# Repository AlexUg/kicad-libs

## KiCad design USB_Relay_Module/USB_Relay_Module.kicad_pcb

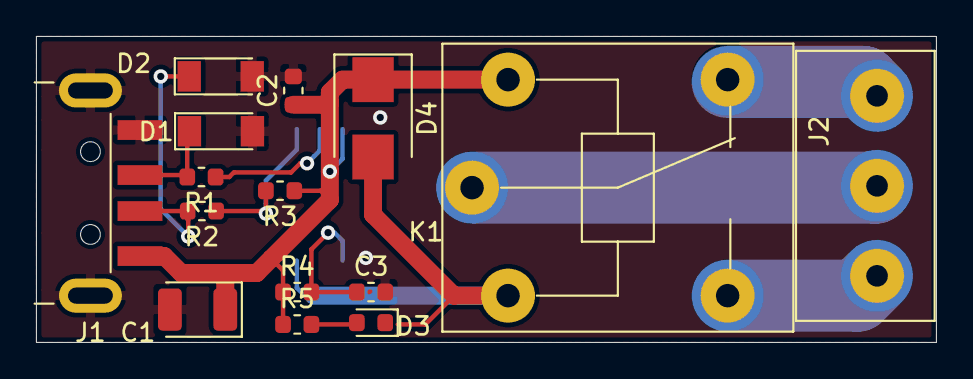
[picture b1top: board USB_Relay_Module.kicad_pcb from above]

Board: 2 copper layers, 50.0 x 17.0 mm, 16 parts (1 on the bottom side), 12 nets.

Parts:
C1: 47uF; CP_EIA-3528-12_Kemet-T
C2, C3: 100n; C_0603_1608Metric
D1, D2: 3.6V; D_MiniMELF
D3: LED; LED_0603_1608Metric
D4: D; D_SMB
J1: USB_A; USB_A_CNCTech_1001-011-01101_Horizontal
J2: OUT; KF301_5.0_3
K1: HLS8
R1, R2: 82; R_0603_1608Metric
R3, R5: 880; R_0603_1608Metric
R4: 10k; R_0603_1608Metric
U1: ATtiny45-20SU; SOIJ-8_5.3x5.3mm_P1.27mm

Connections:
02: J2.2, K1.5
03: J2.1, K1.3
+5V: C1.1, C2.1, D4.1, J1.1, K1.1, R3.1, R4.1, R5.1, U1.8
D+: R1.1, U1.7
D-: R2.1, R3.2, U1.6
GND: C1.2, C2.2, C3.2, D1.2, D2.2, J1.4, J1.5, U1.4
unnamed: D1.1, J1.3, R1.2
unnamed: D2.1, J1.2, R2.2
unnamed: D3.2, R5.2
O1: J2.3, K1.2
Rel: D3.1, D4.2, K1.4, U1.3
Reset: C3.1, R4.2, U1.1

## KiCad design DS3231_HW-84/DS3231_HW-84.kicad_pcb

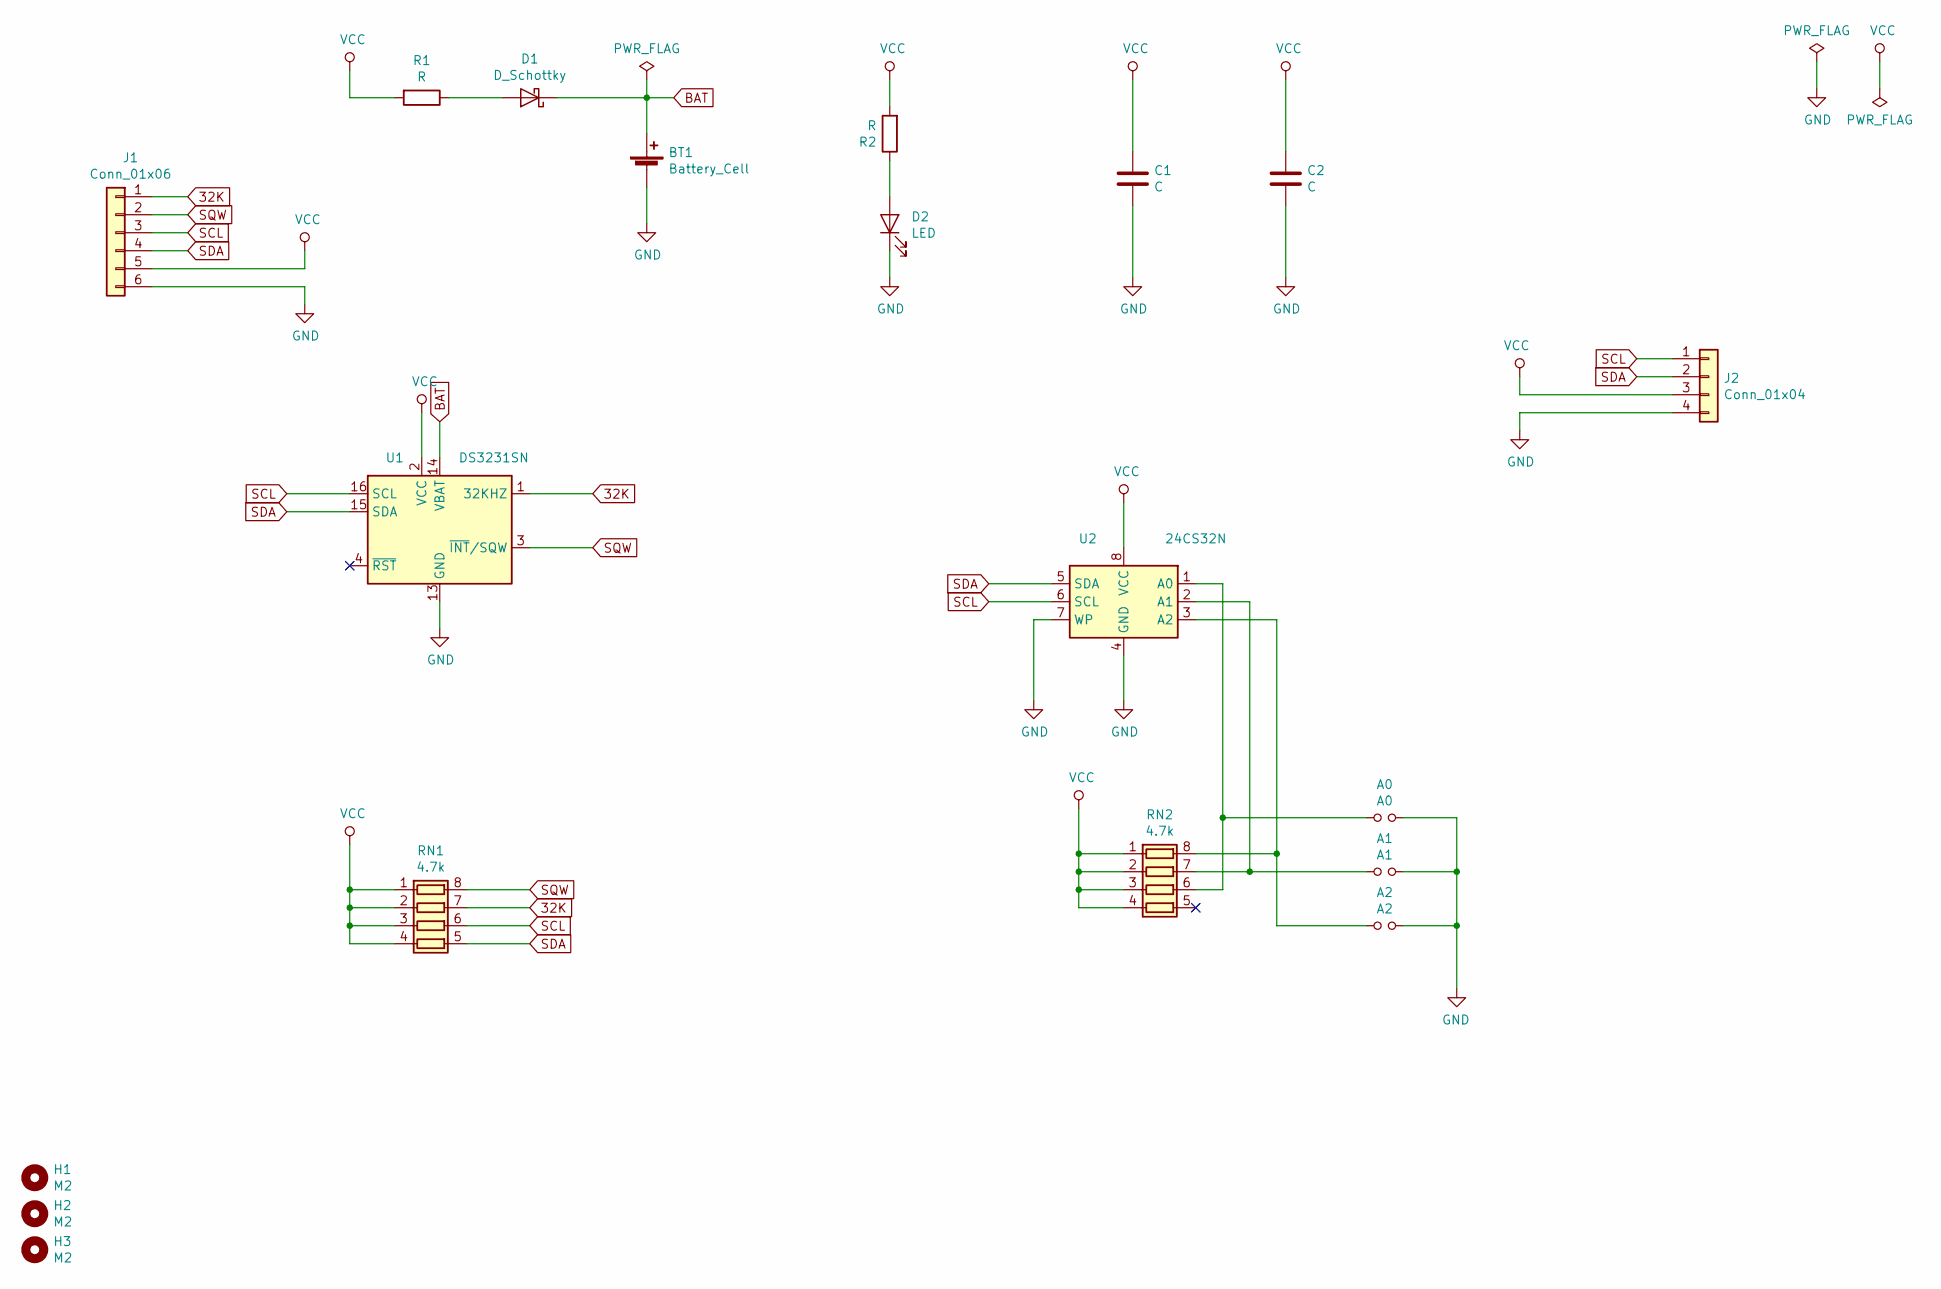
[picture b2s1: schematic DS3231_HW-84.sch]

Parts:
A0: A0; SolderJumper-2_P1.3mm_Open_Pad1.0x1.5mm
A1: A1; SolderJumper-2_P1.3mm_Open_Pad1.0x1.5mm
A2: A2; SolderJumper-2_P1.3mm_Open_Pad1.0x1.5mm
BT1: Battery_Cell; CH224-2032LF
C1, C2: C; C_0805_2012Metric
D1: D_Schottky; D_MELF
D2: LED; LED_0805_2012Metric
H1, H2, H3: M2; MountingHole_2.2mm_M2
J1: Conn_01x06; PinHeader_1x06_P2.54mm_Vertical
J2: Conn_01x04; PinHeader_1x04_P2.54mm_Vertical
R1, R2: R; R_0805_2012Metric
RN1, RN2: 4.7k; R_Array_Convex_4x0603
U1: DS3231SN; SOIC-16W_7.5x10.3mm_P1.27mm
U2: 24CS32N; SOIC-8_3.9x4.9mm_P1.27mm

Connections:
32K: J1.1, RN1.7 (R2.2), U1.1 (32KHZ)
BAT: BT1.1 (+), D1.1 (K), U1.14 (VBAT)
GND: A0.2, A1.2, A2.2, BT1.2 (-), C1.2, C2.2, D2.1 (K), J1.6, J2.4, U1.5 (GND), U1.6 (GND), U1.7 (GND), U1.8 (GND), U1.9 (GND), U1.10 (GND), U1.11 (GND), U1.12 (GND), U1.13 (GND), U2.4 (GND), U2.7 (WP)
unnamed: A0.1, RN2.6 (R3.2), U2.1 (A0)
unnamed: A1.1, RN2.7 (R2.2), U2.2 (A1)
unnamed: A2.1, RN2.8 (R1.2), U2.3 (A2)
unnamed: D1.2 (A), R1.1
unnamed: D2.2 (A), R2.1
SCL: J1.3, J2.1, RN1.6 (R3.2), U1.16 (SCL), U2.6 (SCL)
SDA: J1.4, J2.2, RN1.5 (R4.2), U1.15 (SDA), U2.5 (SDA)
SQW: J1.2, RN1.8 (R1.2), U1.3 (~INT~/SQW)
VCC: C1.1, C2.1, J1.5, J2.3, R1.2, R2.2, RN1.1 (R1.1), RN1.2 (R2.1), RN1.3 (R3.1), RN1.4 (R4.1), RN2.1 (R1.1), RN2.2 (R2.1), RN2.3 (R3.1), RN2.4 (R4.1), U1.2 (VCC), U2.8 (VCC)

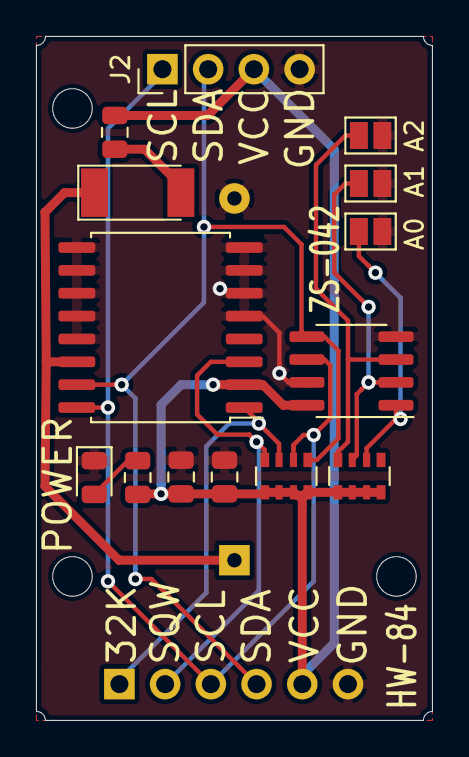
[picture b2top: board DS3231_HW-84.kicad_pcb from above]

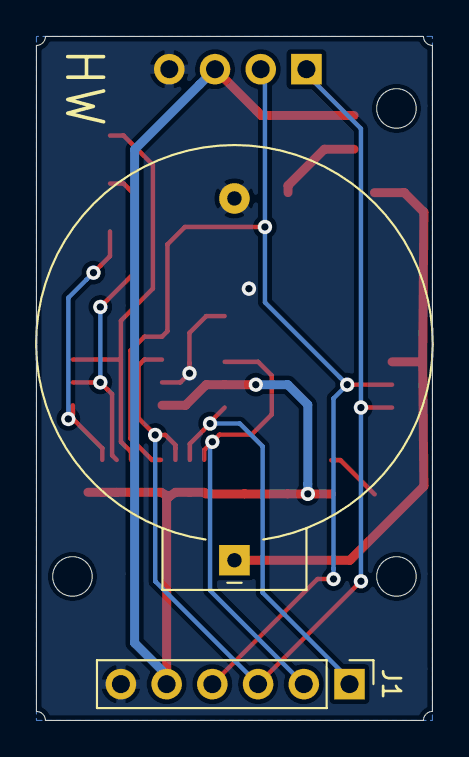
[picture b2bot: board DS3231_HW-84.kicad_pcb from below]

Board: 2 copper layers, 22.0 x 38.0 mm, 19 parts (2 on the bottom side), 12 nets.

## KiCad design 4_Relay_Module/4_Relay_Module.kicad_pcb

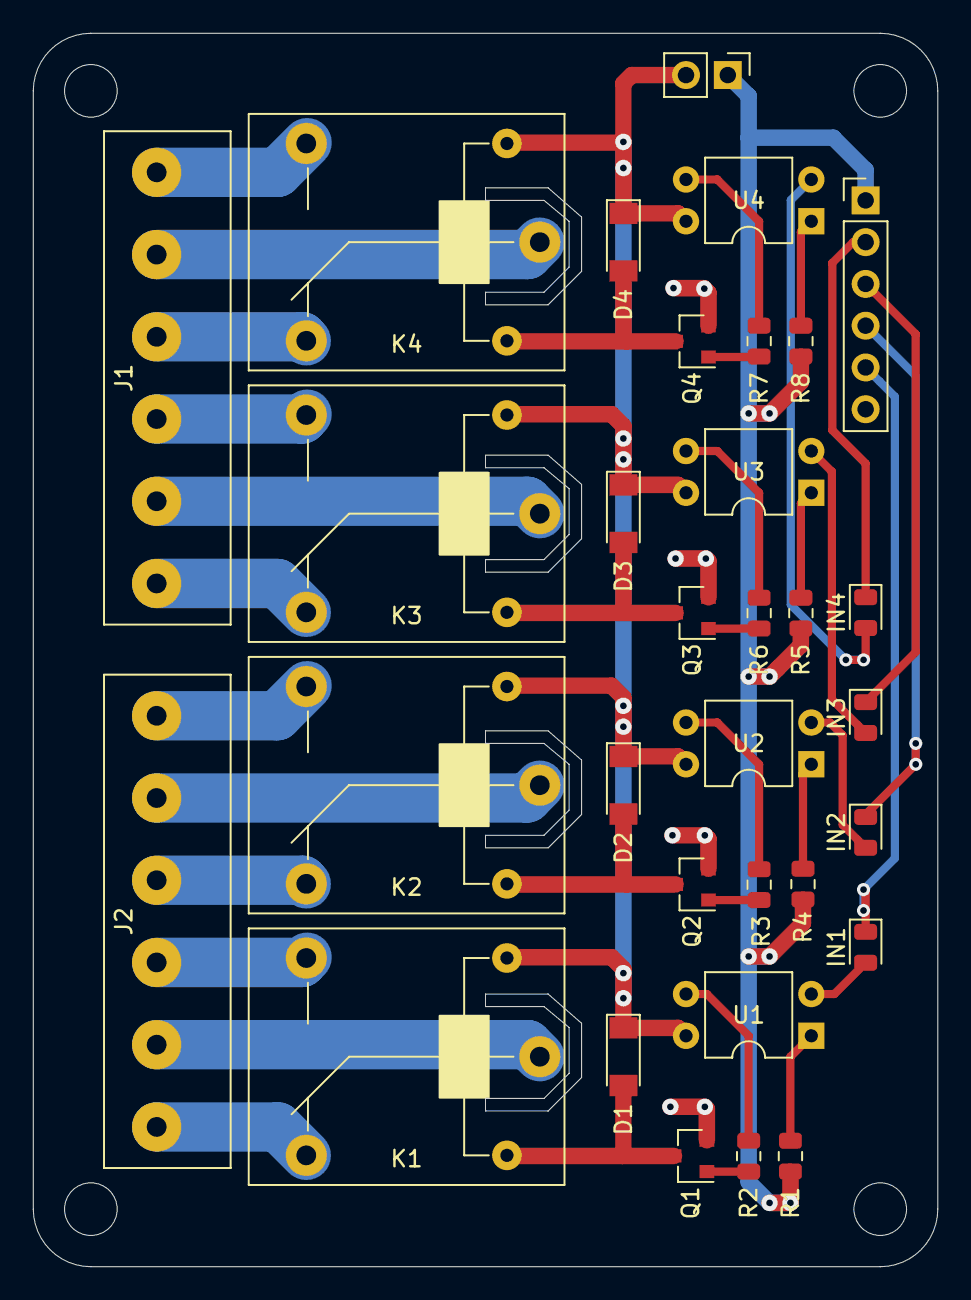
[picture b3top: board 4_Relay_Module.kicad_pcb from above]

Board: 2 copper layers, 55.0 x 75.0 mm, 36 parts (0 on the bottom side), 39 nets.

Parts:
D1, D2, D3, D4: D; D_MiniMELF
H1, H2, H3, H4: MountingHole; MountingHole_3.2mm_M3
IN1, IN2, IN3, IN4: LED; LED_0805_2012Metric
J1, J2: Conn_01x06; KF301_5.0_6
J3: Conn_01x02; PinHeader_1x02_P2.54mm_Vertical
J4: Conn_01x06; PinHeader_1x06_P2.54mm_Vertical
K1, K2, K3, K4: SRD-05VDC-SL-C; SPDT_SRD_05VDC-SL-C
Q1, Q2, Q3, Q4: Q_NPN_BEC; SOT-23
R1, R4, R5, R8: 1k; R_0805_2012Metric
R2, R3, R6, R7: 510; R_0805_2012Metric
U1, U2, U3, U4: 817C; DIP-4_W7.62mm

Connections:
/relay_1/IN: IN1.1, J4.5
/relay_1/OUT_1: J2.5, K1.1
/relay_1/OUT_2: J2.6, K1.4
/relay_1/OUT_3: J2.4, K1.3
/relay_2/IN: IN2.1, J4.4
/relay_2/OUT_1: J2.2, K2.1
/relay_2/OUT_2: J2.3, K2.4
/relay_2/OUT_3: J2.1, K2.3
/relay_3/IN: IN3.1, J4.3
/relay_3/OUT_1: J1.5, K3.1
/relay_3/OUT_2: J1.6, K3.4
/relay_3/OUT_3: J1.4, K3.3
/relay_4/IN: IN4.1, J4.2
/relay_4/OUT_1: J1.2, K4.1
/relay_4/OUT_2: J1.3, K4.4
/relay_4/OUT_3: J1.1, K4.3
GND: J4.6, Q1.2, Q2.2, Q3.2, Q4.2
JD_VCC: D1.1, D2.1, D3.1, D4.1, J3.2, K1.2, K2.2, K3.2, K4.2, U1.4, U2.4, U3.4, U4.4
unnamed: D1.2, K1.5, Q1.3
unnamed: D2.2, K2.5, Q2.3
unnamed: D3.2, K3.5, Q3.3
unnamed: D4.2, K4.5, Q4.3
unnamed: IN1.2, U1.2
unnamed: IN2.2, U2.2
unnamed: IN3.2, U3.2
unnamed: IN4.2, U4.2
unnamed: Q1.1, R2.2
unnamed: Q2.1, R3.2
unnamed: Q3.1, R6.2
unnamed: Q4.1, R7.2
unnamed: R1.2, U1.1
unnamed: R2.1, U1.3
unnamed: R3.1, U2.3
unnamed: R4.2, U2.1
unnamed: R5.2, U3.1
unnamed: R6.1, U3.3
unnamed: R7.1, U4.3
unnamed: R8.2, U4.1
VCC: J3.1, J4.1, R1.1, R4.1, R5.1, R8.1

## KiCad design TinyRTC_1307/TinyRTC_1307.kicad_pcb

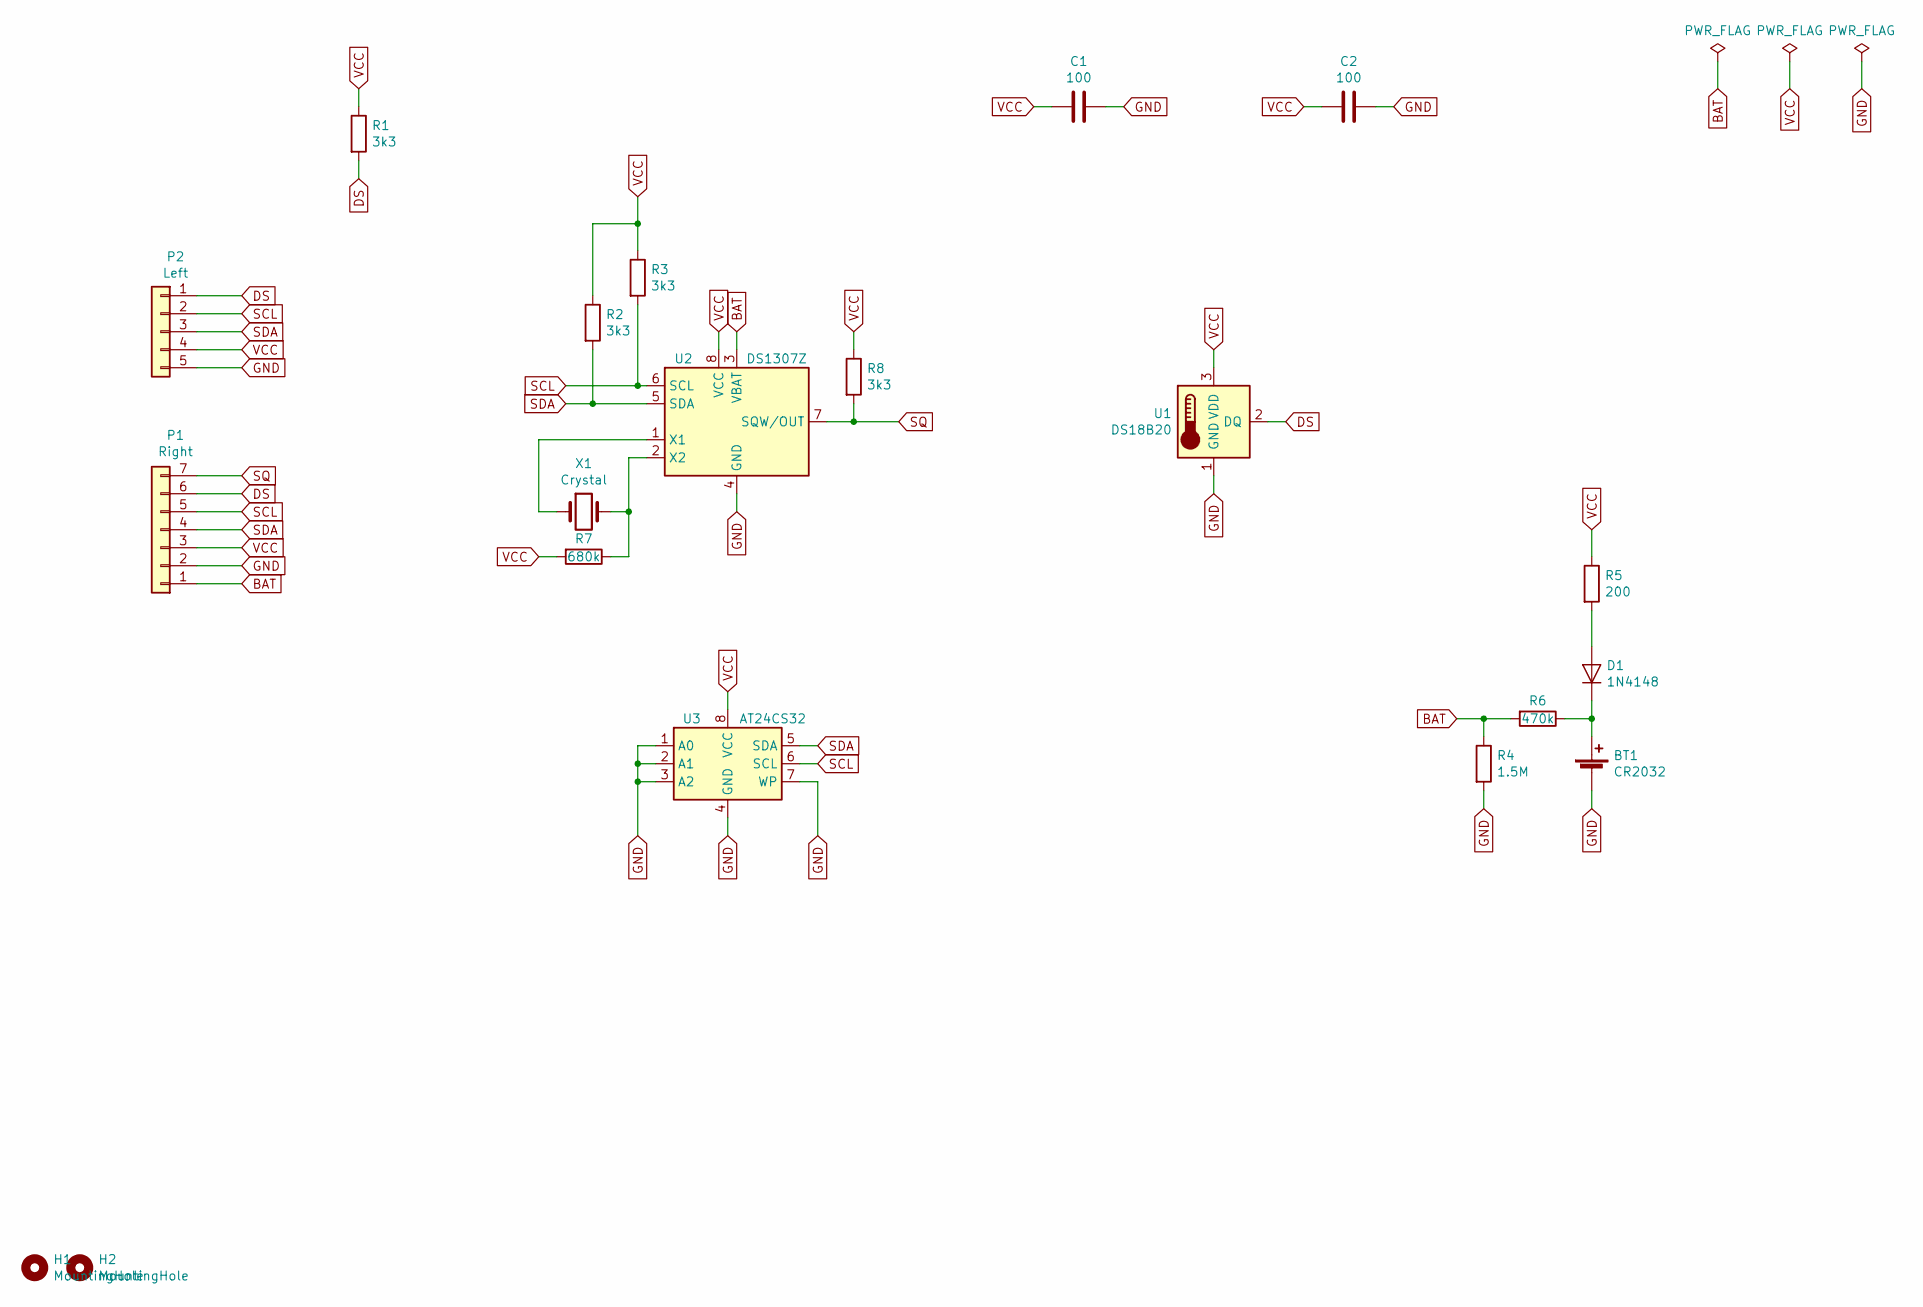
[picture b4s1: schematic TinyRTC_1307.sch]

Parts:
BT1: CR2032; BatteryHolder_Harwin_CR2032
C1, C2: 100; C_0805_2012Metric_Pad1.15x1.40mm_HandSolder
D1: 1N4148; D_MicroMELF_Handsoldering
H1, H2: MountingHole; MountingHole_3mm
P1: Right; PinHeader_1x07_P2.54mm_Vertical
P2: Left; PinHeader_1x05_P2.54mm_Vertical
R1, R2, R3, R8: 3k3; R_0805_2012Metric_Pad1.15x1.40mm_HandSolder
R4: 1.5M; R_0805_2012Metric_Pad1.15x1.40mm_HandSolder
R5: 200; R_0805_2012Metric_Pad1.15x1.40mm_HandSolder
R6: 470k; R_0805_2012Metric_Pad1.15x1.40mm_HandSolder
R7: 680k; R_0805_2012Metric_Pad1.15x1.40mm_HandSolder
U1: DS18B20; TO-92_Inline_Wide
U2: DS1307Z; SOIC-8_3.9x4.9mm_P1.27mm
U3: AT24CS32; SOIC-8_3.9x4.9mm_P1.27mm
X1: Crystal; Crystal_C38-LF_D3.0mm_L8.0mm_Horizontal

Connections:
BAT: P1.1, R4.1, R6.2, U2.3 (VBAT)
DS: P1.6, P2.1, R1.2, U1.2 (DQ)
GND: BT1.2 (-), C1.2, C2.2, P1.2, P2.5, R4.2, U1.1 (GND), U2.4 (GND), U3.1 (A0), U3.2 (A1), U3.3 (A2), U3.4 (GND), U3.7 (WP)
unnamed: BT1.1 (+), D1.1 (K), R6.1
unnamed: D1.2 (A), R5.2
unnamed: R7.1, U2.2 (X2), X1.2
unnamed: U2.1 (X1), X1.1
SCL: P1.5, P2.2, R3.2, U2.6 (SCL), U3.6 (SCL)
SDA: P1.4, P2.3, R2.2, U2.5 (SDA), U3.5 (SDA)
SQ: P1.7, R8.2, U2.7 (SQW/OUT)
VCC: C1.1, C2.1, P1.3, P2.4, R1.1, R2.1, R3.1, R5.1, R7.2, R8.1, U1.3 (VDD), U2.8 (VCC), U3.8 (VCC)

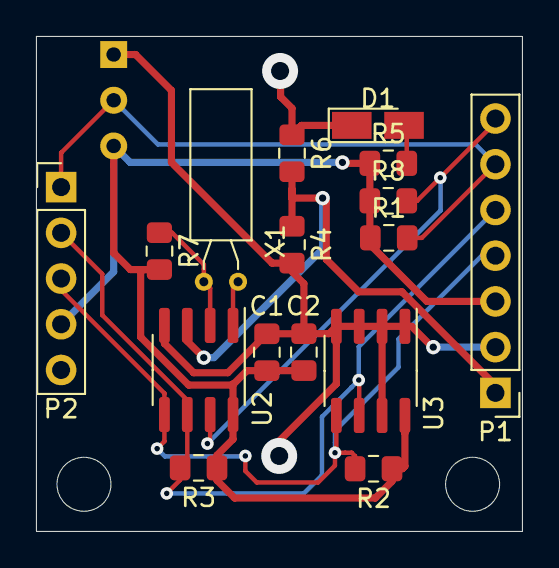
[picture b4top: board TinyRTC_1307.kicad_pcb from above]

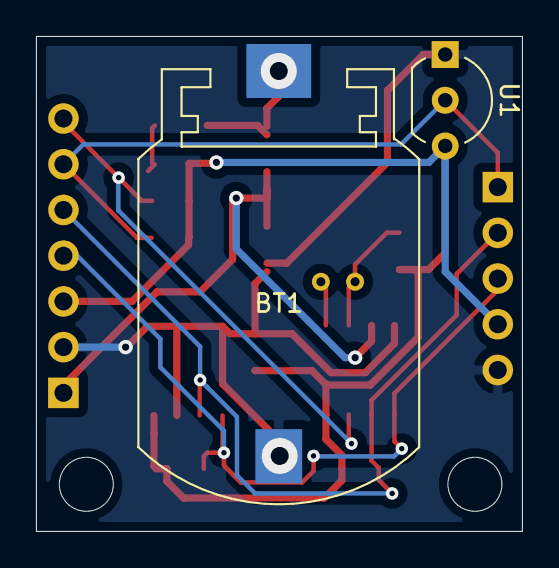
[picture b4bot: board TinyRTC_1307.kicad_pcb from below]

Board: 2 copper layers, 27.0 x 27.5 mm, 20 parts (2 on the bottom side), 11 nets.

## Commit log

2019-12-24 TinyRTC 1307 module: KiCAD project, symbol library, footprints and 3D shapes
2020-01-05 3d model directory name for TinyRTC_1307 was renamed
2020-01-05 Footprint and 3d models for KF-30x connector were added
2020-01-05 Footprint and 3d models for SRD-05VDC-SL-C relay were added
2020-01-06 'rtc_module' renamed to 'rtc_modules'
2020-01-06 Symbol, footprint and 3d models for '4 Relay Module' were added
2020-01-06 '4_Relay_Module' was improved
2020-03-09 MBI5026 symbol
2020-03-09 Connector_Confly/DS-1069-B_1x02_Horizontal footprint and 3D model
2020-04-17 Connector_Confly/DS-1074 was added
2020-04-17 Package_SO_U was added
2020-04-19 DS-1069 was added and DS-1074 was improved
2020-04-19 Arduino-Nano was added
2020-04-21 Minor bug fixes
2020-06-17 Minor changes in Connector_Confly:DS-1069-B_1x02
2021-03-27 Battery CH224-2032LF was added
2021-03-27 DS3231_HW-84 was added
2021-06-24 Relay HLS8 was added
2021-06-24 HLS8 was fixed
2021-06-24 KF_301_5.0_3 was added
2021-06-24 USB Relay module was added
2021-07-01 KF301_5.0_6 was updated
2021-07-01 KF301_5.0_2 was added
2021-07-01 USB-B-292304-1 connector was added
2021-09-12 Pololu motor driver, USB B, Arduino ProMinit were added
2021-12-26 TerminalBlock_Degson was added
2021-12-28 TerminalBlock_Degson was improved
2022-01-06 TerminalBlock_HB9500 3d-models were added
